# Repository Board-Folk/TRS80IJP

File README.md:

# TRS80IJP

A remake of the TRS-80 Model I Japanese (TEC) edition motherboard.

This reposistory contains the BOM, gerbers and Kicad files for a remake of the TEC, Japanese version of the TRS-80 Model I, and some related projects and files to help make it work.

The Japanese board is a rework of the original US edition, some components updated and extra jumpers added to configure the system for 50/60 Hz use, support for an extra character ROM a change to 2114 video RAM chips which are more readily available. The pinout for the Japanese keyboard is different. Because of this for the purposes of making the remake more useful we've added a second pin header for the connection of an original US keyboard. Note the keyboard headers have a 2.5mm pitch.

A replica of the original [TRS-80 Model I 1700069G board is now here](https://github.com/Board-Folk/TRS80IUS).

## Revisions

  * Version 1.1 Updated silkscreen including jumper tables for release.
  
## Version 1.1 Bill-of-Materials

All resistors 1/4W and capacitors 5mm pitch unless specified. Suggested substitutes might be wrong. Any feedback welcome.

|Qty|Reference(s)|Value|Type|Notes|
|:--:|:--:|:--:|:--:|:--:|
|2|R1, R32|100R|Resistor||
|1|R10|270R|Resistor||
|4|R11, R31, R34, R49|10K|Resistor||
|2|R12, R37|220R 1/2W|Resistor||
|1|R13|68 1/2W|Resistor||
|1|R14|2K7|Resistor||
|1|R15|750R|Resistor||
|1|R16|0R33 2W|Resistor||
|2|R17, R23|1K Potentiometer|Resistor||
|4|R2, R18, R19, R28|1K2|Resistor||
|1|R20|100K|Resistor||
|3|R21, R24, R25|3K3|Resistor||
|1|R22|1K5|Resistor||
|1|R26|2K2|Resistor||
|1|R27|12K|Resistor||
|1|R29|2K|Resistor||
|2|R3, R4|7K5|Resistor||
|1|R30|5R6 3W|Resistor||
|2|R33, R51|1M|Resistor||
|1|R35|680K|Resistor||
|1|R36|1.8M|Resistor||
|2|R38, R42|360K|Resistor||
|1|R39|10R|Resistor||
|17|R40, R41, R48, R54, R55, R64-R72, R74, R76, R77|4K7|Resistor||
|1|R43|560K|Resistor||
|5|R44-R47, R50|470K|Resistor||
|1|R5|220K|Resistor||
|2|R52, R53|8K2|Resistor||
|2|R56, R57|910R|Resistor||
|1|R6|75R|Resistor||
|1|R7|47R|Resistor||
|12|R8, R75, R101-R110|330R|Resistor||
|1|R9|120R|Resistor||
|2|RP1, RP2|4K7 Bussed SIP9|Resistor||
|2|C17, C18|220pF|Capacitor||
|44|C2, C8, C20, C22-C39, C41, C44-C49, C51-C59, C63-C69, C71, C72|100nF|Capacitor||
|4|C3, C7, C13, C15|10nF|Capacitor||
|1|C43|100pF|Capacitor||
|1|C60|47pF|Capacitor||
|1|C48|1nF|Capacitor||
|6|C1, C4, C6, C12, C14, C40|10uF 16V|Electrolytic Capacitor||
|1|C10|10000uF 16V|Electrolytic Capacitor||
|1|C19|100uF 16V|Electrolytic Capacitor||
|1|C5|220uF 16V|Electrolytic Capacitor||
|1|C70|22uF 16V|Electrolytic Capacitor||
|1|C9|2200uF 35V|Electrolytic Capacitor||
|3|C11, C16, C57|1nF|Film Capacitor|2.5mm|
|1|C50|2.7nF|Film Capacitor||
|1|CR1|S2V B20 Rectifier|Diode||
|1|CR2|1N4735A Zener|Diode||
|1|CR3|1N4733A Zener|Diode||
|1|CR4|1N4001|Diode||
|4|CR5, CR6, CR7, CR8|1N4148|Diode||
|1|Q1|2SC1815|Transistor||
|2|Q2, Q5|2SA1015|Transistor||
|1|Q3|2SC1499|Transistor||
|1|Q4|2SB-B531|Transistor|Suggested: MJ15016 (See links)|
|1|Q6|2SB-B595|Transistor|Suggested: MJE15029 (See links)|
|2|Z1, Z2|LM723|IC||
|1|Z11|74LS174|IC||
|2|Z12, Z23|74LS245|IC||
|8|Z15, Z16, Z17, Z18, Z19, Z20, Z21, Z22|4116 RAM|IC||
|4|Z24, Z30, Z59, Z66|74LS367|IC||
|1|Z25|LM3900N|IC||
|1|Z26|74LS14|IC||
|1|Z3|SN75452|IC||
|2|Z31, Z47|74LS132|IC||
|2|Z32|74C00|IC||
|2|Z44|74LS00|IC||
|3|Z33, Z46, Z50|74LS04|IC||
|2|Z37, Z38|MCM667X|IC|Character ROM(s) 1 required|
|1|Z39|74LS153|IC||
|2|Z4, Z56|74LS175|IC||
|3|Z40, Z64, Z67|74LS32|IC||
|1|Z41|74LS30|IC||
|1|Z42|2364 ROM|IC||
|1|Z43|2332 ROM|IC||
|2|Z45, Z54|74LS02|IC||
|1|Z48|Z80 DIP40 CPU|IC||
|2|Z49, Z68|74LS244|IC||
|1|Z5|74LS10|IC||
|2|Z51, Z52|74LS08|IC||
|3|Z53, Z62, Z63|74LS74|IC||
|1|Z55|74LS20|IC||
|2|Z57, Z58|74LS166|IC||
|2|Z6, Z65|74LS92|IC||
|1|Z60|74LS11|IC||
|1|Z61|74LS139|IC||
|4|Z7, Z28, Z34, Z35|74LS93|IC||
|6|Z8, Z13, Z14, Z27, Z29, Z36|74LS157|IC||
|2|Z9, Z10|2114 RAM|IC||
|2|CN1,CN3|19 pin header|Other|19 pins used on US|
|1|CN2|9 pin header|Other||
|3|J1-J3|DIN-5 180 Degree Socket|Other||
|10|JP1-JP10|Wire Links|Other||
|1|K1|5V Relay|Other|Suggestion/PN to Follow|
|1|S1|Power Switch|Other|Suggestion/PN to Follow|
|1|S2|Reset Switch|Other|Suggestion/PN to Follow|
|1|Y1|10.6445MHz HC49U|Other|(See links)|

## Notes on the Character ROM

The Japanese board has positions for two character ROMs. These are not regular ROMs.

The first, the original Motorola character ROM now almost unobtainable, on the original board is labelled with the part number 8046773. This is a masked rom programmed at the factory to the specs of Tandy, and is a variation of a stock ROM with a slightly modified character set. This ROM appears to be the same for both the Japanese and US versions of the board that we've seen.

The second character ROM we don't actually have adds a Kana character set which can be switched in and out by jumper setting, and apparently using the Japanese version of the keyboard. This would be fitted at position Z37, and isn't needed for the operation of the board.

The slightly more readily available MCM6674P character ROM can be used for either, but the character layout isn't compatible without modification by the BASIC ROM. If you need to use this we've created an adapter board (see the Extras folder) to modify the character map using an EPROM. Without it you'll end up with hieroglyphics ([see image](https://github.com/Board-Folk/TRS80IJP/blob/main/images/wrongmap.jpg)).

In addition to this, the good people of Tandy Discord have brought up that, way back when, the Gendon3 mod board was available as a substitute for the character ROM chip. This has proven suitable and usable for Japanese Model I though does require a single wired connection outside of the character ROM socket to work. We're currently testing versions of this a board that will fit original US version with a switch between two character sets as well as a board that will work with the built in Kana latch to switch between two character sets for the Japanese board. These have now been uploaded ot the Extras section, with a basic ROM set. More ROMs to use with them will be added as we find them. We're currently a bit stuck finding the Kana character set. There's enough there to get a system working without an original Motorola chip now if need be.

## Links

  [10.6445Mhz HC49U Quartz Crystal (UK)](https://www.mutant-caterpillar.co.uk/shop/product_info.php?products_id=5174)<br>
  [MJ15016 Transistor (Q4 Substitute) (UK)](https://www.cricklewoodelectronics.com/MJ15016.html)<br>
  [MJE15031 Transistor (Q6 Substitute) (UK)](https://www.cricklewoodelectronics.com/MJE15031.html)

## Credits

PCB Layout by Rob Taylor @peepouk. Schematics recreated by Ian Cudlip @grandoldian, and Chrissy @chris_jh.

## Thanks

  * The rest of the Board Folk Team
  * Adrian Black and friends for their test ROM which has been invaluable during testing. [TRS-80 Diagnostic ROM](https://github.com/misterblack1/trs80-diagnosticrom).

## Legal

As the product of this project is a replica of a proprietary product, the the author makes no claim of copyright to the schematics nor PCB layouts and releases these into the public domain, solely for the purposes of study and historical preservation.

You are free to produce PCBs based on this project's designs at your own risk and without limitation, for your own use or for sale and/or repair at a reasonable price. Attribution is appreciated. The authors are not obliged to provide support of any kind. 

Under no circumstances will the authors be held responsible or liable in any way for losses, damages or costs resulting from the use of the information and/or resources of this project. 

The resources are provided "as-is" without warranty of any kind, either expressed or implied, including, but not limited to, the implied warranties of merchantability and fitness for a particular purpose.

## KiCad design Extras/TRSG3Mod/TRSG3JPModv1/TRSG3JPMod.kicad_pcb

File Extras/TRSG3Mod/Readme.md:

# G3Mod and G3JPMod Character ROM Substitute Boards

Two versions of an updated character ROM substitute board based on the original Gendon3 Mod board that uses an 2716 or 2532 EPROM to provide the character set without an original Motorola chip. They require a soldered wire connection not provided by the character ROM socket.

Both boards allow the use of a 2716 2KByte EPROM to provide a single character set to the system, or a 2532 EPROM to provide two selectable 2KByte alternative ROM images.

Each board provides two pin connections, the first of which needs to be connected to L8 on an unmodified TRS-80 Model I for the board to work as standard. The second pin same as provided by the original Gendon3 is out of the scope of this project at this time.

Not suitable for a 2732 EPROM as the pinout's slightly different for the upper 2K. Might do other versions of these if needed, but have found the Hitachi HN462532G 2532 chips readily available new so haven't as yet.

## TRSG3Mod

The first board, G3Mod is primarily intended for use on the original US TRS-80 Model I (physical layout) and has a switch to select between the two 2K halves of the EPROM. 

Pin 1 wire connection should be to Z12 pin 11, on an original US board, and Z35 pin 11 on a Japanese board.

The BOM is simple, just a 0805 or 0402 10K resistor if you want to use the selector switch, the switch which itself, a standard single SPST 2.54mm pitch DIP, a coupling wire to the connection point and the 24 pin EPROM itself. It's nice to put it in a socket for reprogramming. To just use the first half of the 2532 without a switch put a solder blob over the 0402 position.

## TRSG3JPMod

The second board, G3JPMod is intended for use with the Japanese TRS-80 Model I, the two halves of the ROM being selected either by jumper settings on the main board, or by keyboard selection.

Pin 1 wire connection should be to Z35 pin 11.

Just requires a coupling wire to the connection point and the 24 pin EPROM itself with a socket if need be.

## ROMS

ROM images for both boards. More to follow.

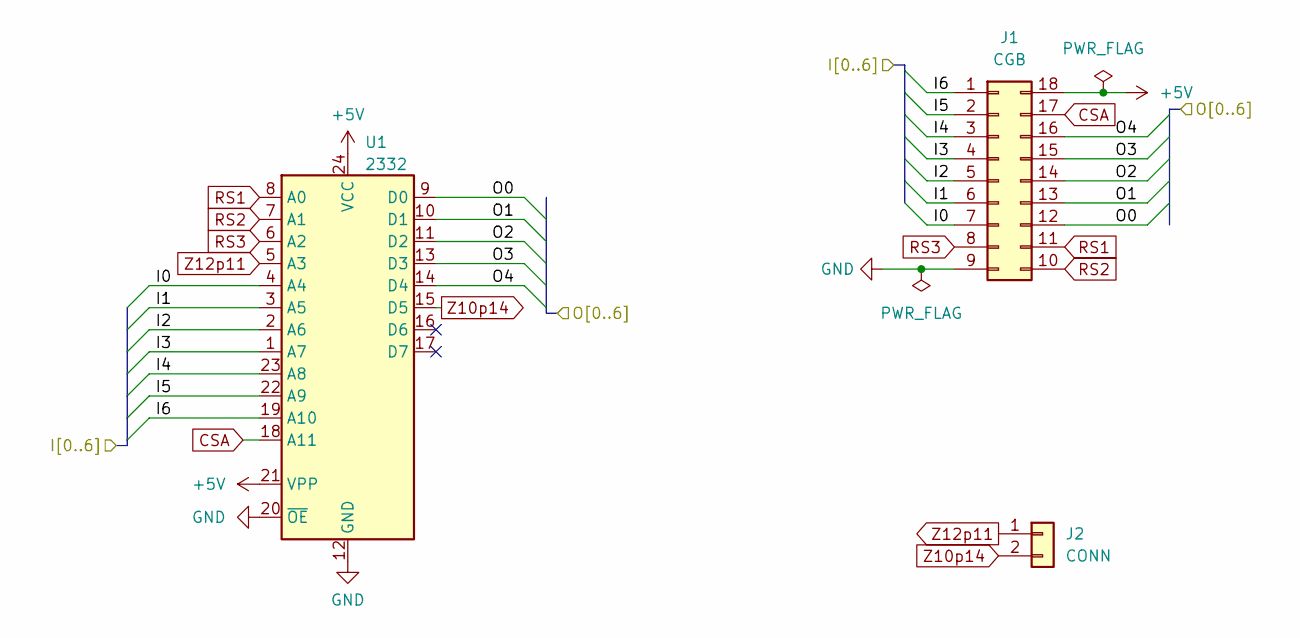
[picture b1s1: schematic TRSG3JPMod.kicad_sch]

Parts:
J1: CGB; CHARPLUG
J2: CONN; PinHeader_1x02_P2.54mm_Vertical
U1: 2332; DIP-24_W15.24mm

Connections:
+5V: J1.18, U1.21 (VPP), U1.24 (VCC)
/I0: J1.7, U1.4 (A4)
/I1: J1.6, U1.3 (A5)
/I2: J1.5, U1.2 (A6)
/I3: J1.4, U1.1 (A7)
/I4: J1.3, U1.23 (A8)
/I5: J1.2, U1.22 (A9)
/I6: J1.1, U1.19 (A10)
/O0: J1.12, U1.9 (D0)
/O1: J1.13, U1.10 (D1)
/O2: J1.14, U1.11 (D2)
/O3: J1.15, U1.13 (D3)
/O4: J1.16, U1.14 (D4)
CSA: J1.17, U1.18 (A11)
GND: J1.9, U1.12 (GND), U1.20 (~OE)
RS1: J1.11, U1.8 (A0)
RS2: J1.10, U1.7 (A1)
RS3: J1.8, U1.6 (A2)
Z10p14: J2.2, U1.15 (D5)
Z12p11: J2.1, U1.5 (A3)

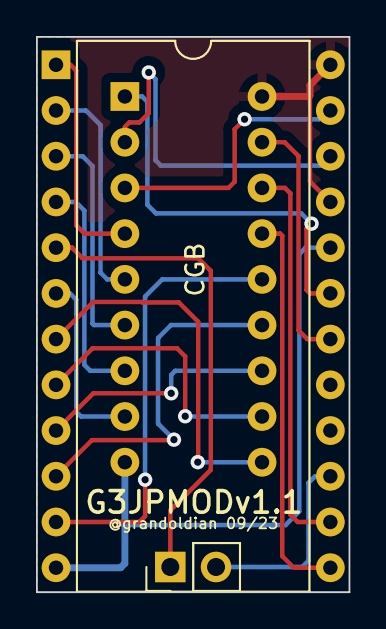
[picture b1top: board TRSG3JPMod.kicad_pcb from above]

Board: 2 copper layers, 17.4 x 30.9 mm, 4 parts (1 on the bottom side), 20 nets.

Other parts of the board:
G1: LOGO8; BF8

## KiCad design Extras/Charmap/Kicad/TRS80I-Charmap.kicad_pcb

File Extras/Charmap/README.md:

# TRS-80 Model I Character Map Adapter Board

The original masked TRS-80 character ROM is now difficult to obtain. This is a simple adapter board to allow the use of the more readily available MCM6674P character ROM with the TRS-80 Model I BASIC ROM, possibly others too with the right map. It uses a standard 24 pin EEPROM/EPROM to map the original address lines coming in to alternatives compatible with your available character ROM to create the correct video output. Without it BASIC will give you garbage ([see image](https://github.com/Board-Folk/TRS80IJP/blob/main/images/wrongmap.jpg)).

The character ROM itself is a 7 bit ROM giving 128 characters. The character map a simple byte array providing the location of the alternative character of the replacement character in the substitute ROM used for each position.

The map board incorporates a single two position switch to allow the EPROM to be programmed with two alternative maps - two lots of 128 bytes which are positioned at the start of the EPROM.

The Kicad project for the board is in the Kicad folder with the zip file TRS80I-Charmap-Gerberv1.zip being the Gerber of this project. The file out.rom is my interpretation of how the MCM6674P should be represented to BASIC and this was generated using the C code trs80map.c. Please feel free to make your own maps. :-)

I've used an Atmel 28C16 as it's easy to re-flash.

## Credits

By Ian Cudlip @grandoldian November 2022.

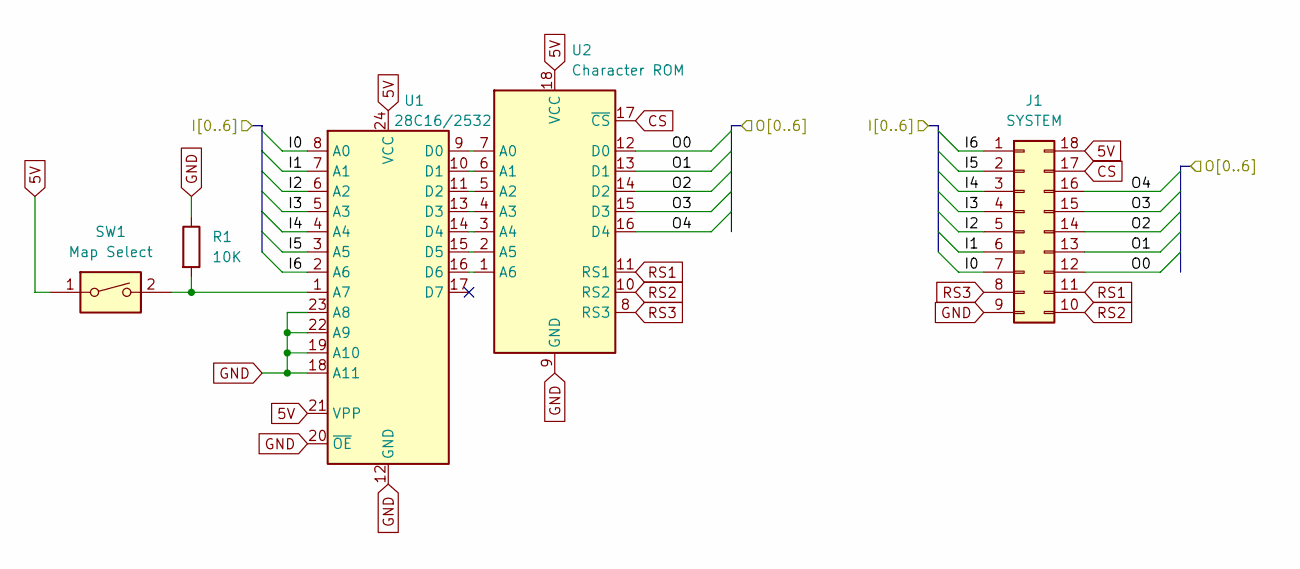
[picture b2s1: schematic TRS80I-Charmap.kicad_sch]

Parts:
J1: SYSTEM; DIP-18_W7.62mm
R1: 10K; R_0805_2012Metric
SW1: Map Select; SW_DIP_SPSTx01_Slide_6.7x4.1mm_W7.62mm_P2.54mm_LowProfile
U1: 28C16/2532; DIP-24_W15.24mm_Socket
U2: Character ROM; DIP-18_W7.62mm_Socket

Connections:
5V: J1.18, SW1.1, U1.21 (VPP), U1.24 (VCC), U2.18 (VCC)
/I0: J1.7, U1.8 (A0)
/I1: J1.6, U1.7 (A1)
/I2: J1.5, U1.6 (A2)
/I3: J1.4, U1.5 (A3)
/I4: J1.3, U1.4 (A4)
/I5: J1.2, U1.3 (A5)
/I6: J1.1, U1.2 (A6)
/O0: J1.12, U2.12 (D0)
/O1: J1.13, U2.13 (D1)
/O2: J1.14, U2.14 (D2)
/O3: J1.15, U2.15 (D3)
/O4: J1.16, U2.16 (D4)
CS: J1.17, U2.17 (~CS)
GND: J1.9, R1.1, U1.12 (GND), U1.18 (A11), U1.19 (A10), U1.20 (~OE), U1.22 (A9), U1.23 (A8), U2.9 (GND)
unnamed: R1.2, SW1.2, U1.1 (A7)
unnamed: U1.9 (D0), U2.7 (A0)
unnamed: U1.10 (D1), U2.6 (A1)
unnamed: U1.11 (D2), U2.5 (A2)
unnamed: U1.13 (D3), U2.4 (A3)
unnamed: U1.14 (D4), U2.3 (A4)
unnamed: U1.15 (D5), U2.2 (A5)
unnamed: U1.16 (D6), U2.1 (A6)
RS1: J1.11, U2.11 (RS1)
RS2: J1.10, U2.10 (RS2)
RS3: J1.8, U2.8 (RS3)

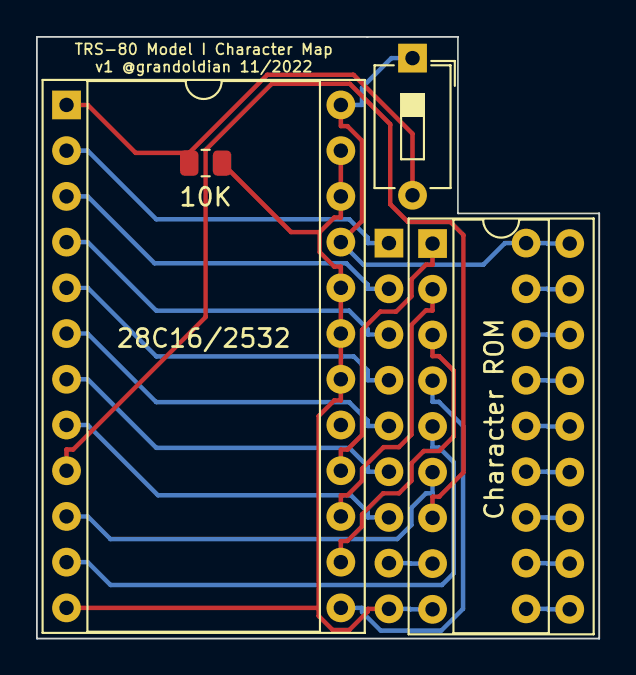
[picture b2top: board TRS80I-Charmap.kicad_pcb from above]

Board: 2 copper layers, 31.2 x 33.4 mm, 5 parts (0 on the bottom side), 26 nets.

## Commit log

2023-08-14 Initial Update
2023-08-14 Image Smaller
2023-08-14 Image Smaller Again
2023-08-16 Charmap Readme Update
2023-08-20 Publish Kicad/BOM
2023-08-20 Remove some old
2023-08-21 Update README.md (C11, C16, C57 note)
2023-09-17 Large G3 Mod Board Images
2023-09-17 Upload G3Mod & G3JPMod
2023-09-17 Minor corrections
2023-09-17 Update TRSG3JPMod and Images
2023-09-25 Update Z32 label, Sync v1.1 Schematic to PCB
2023-09-25 iBOM Update
2023-12-29 Readme updates
2023-12-29 Revert "Readme updates"
    This reverts commit 050a3ce6f3eb21dcc06767f988489fab4565d0ca.
